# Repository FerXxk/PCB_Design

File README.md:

# KiCad PCB Design Automation with Docker

Este proyecto integra un ESP32, un regulador HT7333A y un sensor siguiendo el esquema proporcionado.

## Requisitos
- Docker instalado.
- Make (opcional, facilita la ejecución).

## Instrucciones de Uso

### 1. Construir la imagen de Docker
Si es la primera vez, construye la imagen que contiene KiCad 8 y las herramientas necesarias:
```bash
docker build -t kicad-automation .
```

### 2. Ejecutar la Automatización
Puedes usar el `Makefile` para generar los archivos de fabricación (Gerbers, BOM, PDF) automáticamente:

**En Linux/Mac:**
```bash
docker run --rm -v $(pwd):/project kicad-automation make all
```

**En Windows (PowerShell):**
```powershell
docker run --rm -v ${PWD}:/project kicad-automation make all
```

### Archivos Generados
- `fabrication/gerbers/`: Archivos para enviar a fabricar la PCB.
- `fabrication/bom/`: Listado de componentes (CSV).
- `docs/`: Esquemático y diseño de PCB en formato PDF para revisión rápida.

## Notas sobre el Diseño
- El sensor está conectado a **GPIO34** del ESP32.
- La alimentación del sensor proviene de la salida de **3.3V** del HT7333A.
- Se ha incluido un borde de placa de **100mm x 50mm** en el archivo `.kicad_pcb`.

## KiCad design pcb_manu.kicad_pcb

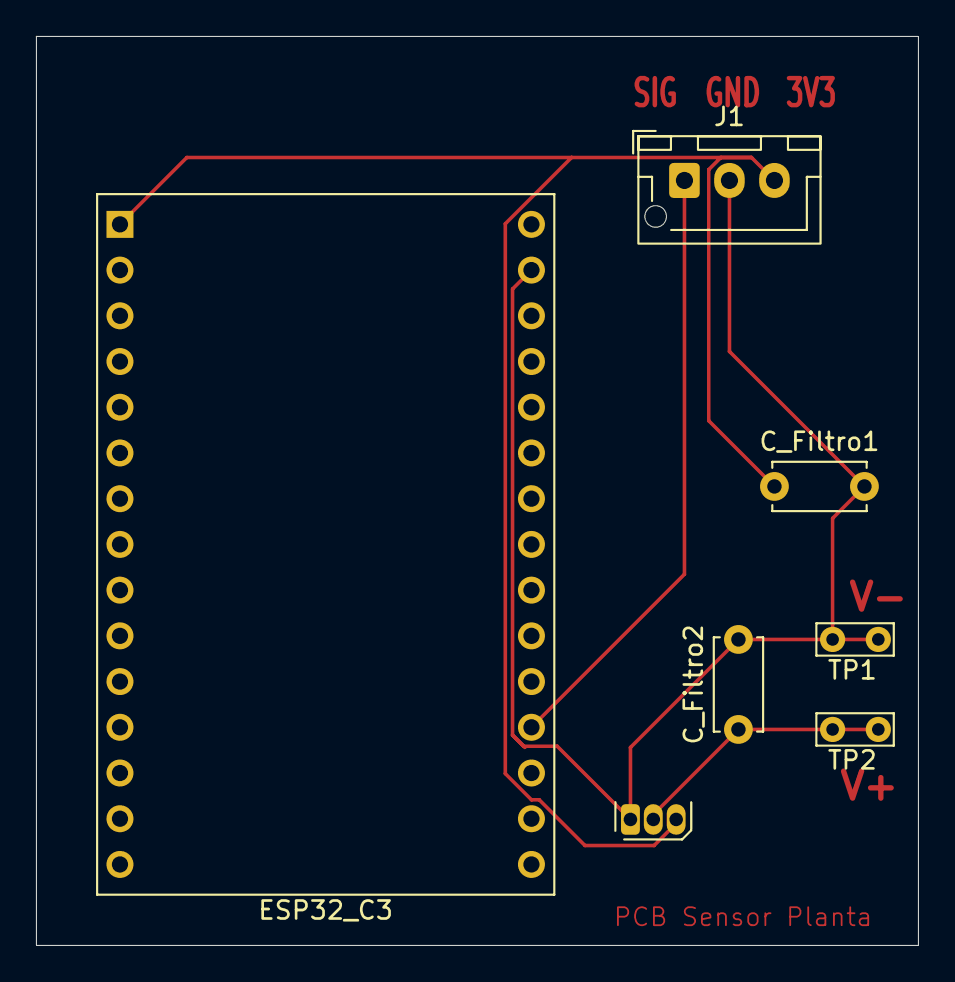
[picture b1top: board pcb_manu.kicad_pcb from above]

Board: 2 copper layers, 49.0 x 50.5 mm, 7 parts (0 on the bottom side), 4 nets.

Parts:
C_Filtro1, C_Filtro2: 10uF; C_Disc_D5.0mm_W2.5mm_P5.00mm
ESP32_C3: Conn_02x15_Counter_Clockwise; ESP32-C3-DevKitM-1
J1: Conn_01x03_Pin; JST_XH_B3B-XH-AM_1x03_P2.50mm_Vertical
Regulador: MCP1700x-330xxMB; TO-92S
TP1, TP2: TestPoint; TestPoint_Bridge_Pitch2.54mm_Drill0.7mm

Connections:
/3V3: C_Filtro1.1, ESP32_C3.1, J1.3, Regulador.3 (VO)
/D34: ESP32_C3.19, J1.1
/GND: C_Filtro1.2, C_Filtro2.2, ESP32_C3.29, J1.2, Regulador.1 (GND), TP1.1
/Vin: C_Filtro2.1, Regulador.2 (VI), TP2.1

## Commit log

2026-02-17 feat: pcb v1
